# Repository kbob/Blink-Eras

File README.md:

# Eras of Blinking

Blinking an LED as it was done in the 1970s (555) and the 1990s (AVR).

I am using this project to learn KiCAD and SMT fabrication.  Also
learning to use pogo pins to flash a microcontroller.

# The ISP Pogo Jig

I designed and built a jig to hold pogo pins against the board's ISP
headers to program the AVR.  In the end, I did not use the jig; it did not
press the pogo pins against the contacts hard enough to make a solid
connection.

I found Nick Sayers'
[AVR ISP Pogo Adapter v0.5](https://oshpark.com/shared_projects/iyo8KOe5)
on OSH Park and ordered it.  I soldered the pogo pins to two boards 7
mm apart so the pins would be well aligned.

I use [ecad.io](https://ecad.io) to create STEP files representing the
boards' geometric shapes.  I imported the boards into Fusion 360,
modeled a pogo pin, and designed a jig around them.

The [Fusion 360 model is here](http://a360.co/2aq1vVH).  

If I did it again, I would do it very differently.  I think I would
flip the jig over so the board sits on top, with some kind of latch to
hold it in place.

# Differences between v1.0 and v1.1

  - Shrink through holes for battery clip.
  - Eliminate rectangle around "AVR" lettering.
  - Change "555" and "1971" lettering to get better separation.
  - Enlarge "CR2032" lettering.
  - Enlarge presidents' caricatures, just keep the faces.
  - Increment the silkscreen version number.

# Resources

[Getting to Blinky 4.0](https://www.youtube.com/playlist?list=PLy2022BX6Eso532xqrUxDT1u2p4VVsg-q)
Video tutorials for KiCAD 4.0

[Flashing LED Circuit](http://www.555-timer-circuits.com/flashing-led.html)
Simple 555 astable circuit.  Cribbed mercilessly.

[How to Build an AVR Blinking LED Circuit](http://www.learningaboutelectronics.com/Articles/AVR-blinking-LED-circuit.php)

[Programming an ATtiny w/ Arduino 1.6](http://highlowtech.org/?p=1695)

[LED Resistor Calculator](http://led.linear1.org/1led.wiz)

[3D KiCAD Parts tutorial](http://happyrobotlabs.com/posts/tutorials/tutorial-3d-kicad-parts-using-openscad-and-wings3d/)

[KiCAD graphics tutorial](http://blog.komar.be/making-pcb-artwork-in-kicad/)

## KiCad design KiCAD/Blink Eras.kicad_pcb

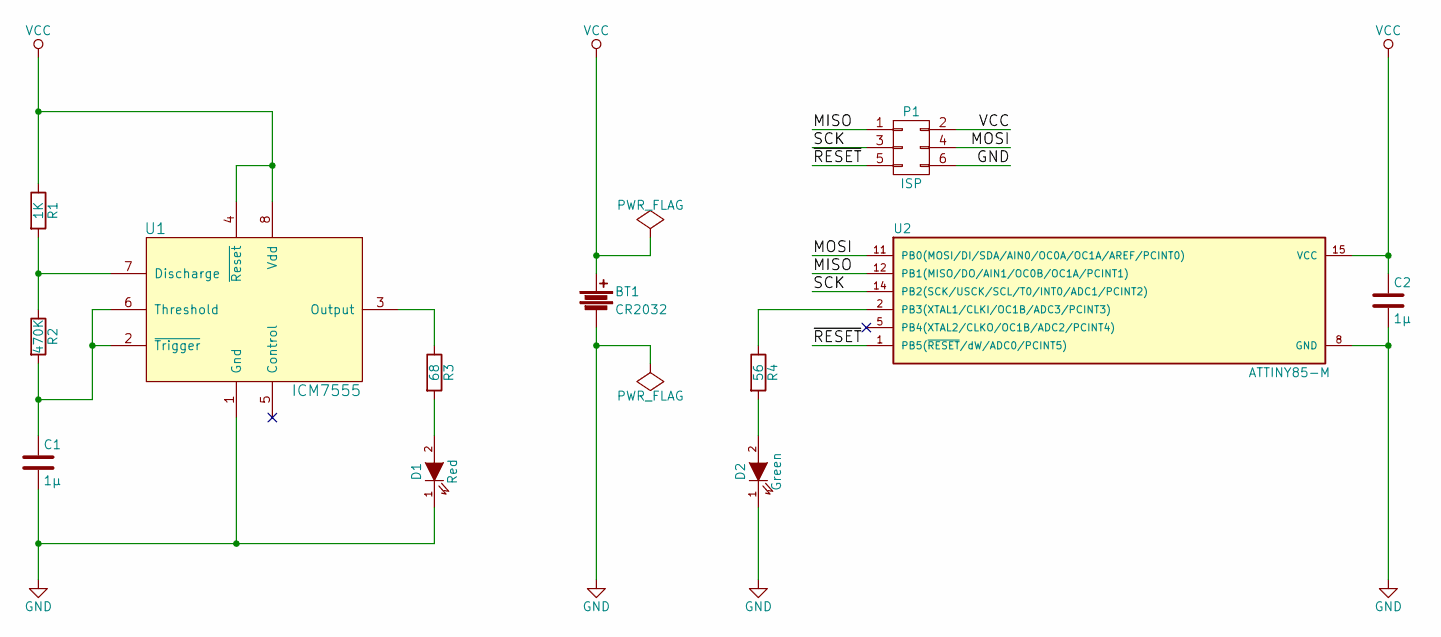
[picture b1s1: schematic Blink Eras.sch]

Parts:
BT1: CR2032; BK-913
C1, C2: 1µ; C_0603_HandSoldering
D1: Red; LED_0603
D2: Green; LED_0603
P1: ISP; ISP_Pogo_3-thru
R1: 1K; R_0603_HandSoldering
R2: 470K; R_0603_HandSoldering
R3: 68; R_0603_HandSoldering
R4: 56; R_0603_HandSoldering
U1: ICM7555; SOIC-8_3.9x4.9mm_Pitch1.27mm
U2: ATTINY85-M; QFN-20-1EP_4x4mm_Pitch0.5mm

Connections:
/MISO: P1.1, U2.12 (PB1(MISO/DO/AIN1/OC0B/OC1A/PCINT1))
/MOSI: P1.4, U2.11 (PB0(MOSI/DI/SDA/AIN0/OC0A/OC1A/AREF/PCI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)
/SCK: P1.3, U2.14 (PB2(SCK/USCK/SCL/T0/INT0/ADC1/PCINT2))
/~RESET~: P1.5, U2.1 (PB5(~RESET~/dW/ADC0/PCINT5))
GND: BT1.2, C1.2, C2.2, D1.1 (K), D2.1 (K), P1.6, U1.1 (Gnd), U2.8 (GND)
unnamed: C1.1, R2.2, U1.2 (~Trigger~), U1.6 (Threshold)
unnamed: D1.2 (A), R3.2
unnamed: D2.2 (A), R4.2
unnamed: R1.2, R2.1, U1.7 (Discharge)
unnamed: R3.1, U1.3 (Output)
unnamed: R4.1, U2.2 (PB3(XTAL1/CLKI/OC1B/ADC3/PCINT3))
VCC: BT1.1, C2.1, P1.2, R1.1, U1.4 (~Reset~), U1.8 (Vdd), U2.15 (VCC)

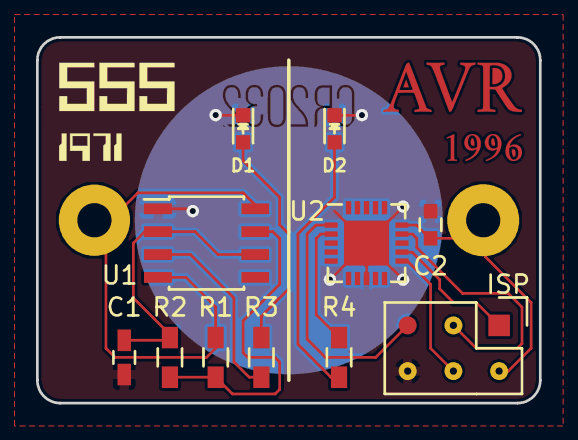
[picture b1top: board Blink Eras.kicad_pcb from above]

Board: 2 copper layers, 27.9 x 20.3 mm, 12 parts (1 on the bottom side), 12 nets.

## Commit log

2016-07-07 Initial commit. Schemmatic drawn but fails DRC.
2016-07-07 Schematic cleanup. Passes ERC.
2016-07-07 Inverted power flag.
2016-07-07 Removed *.bak files.
2016-07-07 Now git will ignore *.bak.
2016-07-07 Added Arduino sketch for ATtiny.
2016-07-07 Footprints, values, refinement.
2016-07-07 Moved Arduino and KiCAD into separate subdirectories.
2016-07-07 Added README and datasheets.
2016-07-07 Added CC-by-4.0 license.
2016-07-07 Created footprint for BK-913 battery holder.
2016-07-08 Created 3D model of BK-913 coin cell retainer in FreeCAD.
2016-07-09 PCB is routed.
2016-07-09 Battery holder was upside down. Corrected.
2016-07-10 Removed the w_battery_holders library, as it doesn't have the right part.
2016-07-10 Changed battery holder's 3D model reference to be project-relative.
2016-07-10 Removed netlist file from the repository. It is autogenerated.
2016-07-10 Hide passive component values.
2016-07-10 Ignore autosave files.
2016-07-10 New layout makes the pogo pins fit.
2016-07-10 Routed pogo pins.
2016-07-10 Tied QFN20's ground pad to ground.
2016-07-10 Big round battery contact, six vias to ground plane.
2016-07-10 Moved ATtiny bypass cap.
2016-07-10 Cleaned up extraneous traces inside pads.
2016-07-10 GND zone did not quite cover the right edge of the board. Fixed.
2016-07-11 Artwork, first draft..
2016-07-13 README: added link for KiCAD graphics tutorial.
2016-07-13 Updated all artwork. Many layers.
2016-07-14 Added animation to README.
2016-07-14 Sped up animation.
2016-07-24 Removed unused footprints.
2016-08-03 Removed duplicate frame.
2016-08-03 All files for ISP pogo jig
2016-08-03 Stuffing guide.
2016-08-03 Wrote a paragraph in README about redesigning the pogo pin jig.
2016-08-03 Archived off v1.0 of KiCAD files.
2016-08-04 Shrank battery through holes, re-did CR2032 lettering.
2016-08-04 v1.1 changes
    - Shrink through holes for battery clip.
    - Eliminate rectangle around "AVR" lettering.
    - Change "555" and "1971" lettering to get better separation.
    - Enlarge "CR2032" lettering.
    - Enlarge presidents' caricatures, just keep the faces.
    - Increment the silkscreen version number.
